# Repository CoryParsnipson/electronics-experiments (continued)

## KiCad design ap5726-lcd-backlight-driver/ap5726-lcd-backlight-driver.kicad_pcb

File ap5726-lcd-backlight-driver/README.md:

# ap5726-lcd-backlight-driver

This is a design using the AP5726 integrated chip to drive backlights on small (cellphone-sized) LCD screens. The requirements for many screens are idiosyncratic, requiring support for high voltages of up to 18-30V and 40mA of *constant* current to drive two parallel strings of 4-6 white LEDs in series.

## KiCAD Version

Current version: KiCAD 7.0.2.

This was originally made with KiCAD 7.0.2.

## Description

The backlight in LCD displays ranging from 3-7 inches in size consist of two rows of white surface mount LCDs in parallel, spanning the top and bottom edges of the screen. Each branch contains 3-6 LEDs. The LCD screen also has special diffuse material that lets the light from the LEDs spread out across the surface of the screen. One may think of the backlight in a schematic as such:

The specifications here claim that the LEDs should be driven with a maximum of 40mA of current, and the voltage drop across the entire LED circuit will be 18.2V. You can drive with lower current, and the screen will be less bright.

It is important to find a dc-converter or regulated power supply that is specifically constant current so that the screen backlight will not flicker randomly during operation.

### Schematic

The schematic of this breakout board is fairly minimal and based on [page 12 of the AP5726 datasheet](https://www.diodes.com/assets/Datasheets/AP5726.pdf).

My schematic has the addition of a solder jumper on the LED\_K pin and a test pad on the FB pin. This is because the intention is to dim the lights using the ENABLE pin, but in case I wanted to use a filtered pwm signal, I would be able to splice a voltage and resistor with the solder jumper.

For more information about this, see the "LED Dimming" section below.

#### Inductor Selection

The datasheet recommends inductors between 10 and 22 uH (micro henries). The inductor should have low core losses at 1.2 MHz and low DCR (copper wire resistance). Lastly the inductor's current saturation should exceed the peak input current of the design.

The recommended parts from the AP5726 datasheet were mostly obsolete or out of stock. I ended up using the [LQH44PN220](https://www.digikey.com/en/products/detail/murata-electronics/LQH44PN220MPRL/16516913), which seems to satisfy all of the constraints described above. (290milliOhm DCR and saturation current at 1.05A)

##### Calculating Peak Input Current and Minimum Input Current

The calculation of peak and minimum input current is partially described [here](https://components101.com/articles/boost-converter-basics-working-design#:~:text=a%20boost%20converter.-,Boost%20Converter%20Design,and%20current%20independently%2C%20the%20product%20of%20which%20is%20our%20output%20power.,-STEP%20%E2%80%93%202).

> STEP – 1
> 
> To begin with, we need a thorough understanding of what our load requires. It is highly recommended (from experience) that if you attempt to build a boost converter at the beginning it is very important to know the output voltage and current independently, the product of which is our output power.
> 
> STEP – 2
> 
> Once we have the output power, we can divide that by the input voltage (which should also be decided) to get the average input current needed.
> 
> We increase the input current by 40% to account for ripple. This new value is the peak input current.
> 
> Also the minimum input current is 0.8 times the average input current, so multiply the average input current by 0.8.
> 
> Now that we have peak and minimum current, we can calculate the total change in current by subtracting the peak and minimum current.

We can work backwards for our application. We know that we need to deliver 40mA of current to the LEDs, which will have approximately 18.2V across them.

`P = i * v = 0.04 * 18.2 = 0.728 Watts`

Now for step 2, dividing the output power by input voltage, which will be 3.3V here. (5V will work too, but my design is going to be powered by a 3.3V supply).

`I_avg = 0.728 / 3.3 = 0.221 Amps`

So next nominal peak input current is this average value times 140%:

`I_peak_nom = 0.221 * 1.4 = 0.309 Amps`

But we must also take into account the efficient of our converter (it's about 75-80% according to the datasheet). So lets go with 70% to be safe, meaning we need to multiply by 1.43:

`I_peak = 0.309 * 1.43 = 0.441 Amps`

And to get minimum input current, we can multiply average input current by 0.8 and 1.43 to account for converter efficiency:

`I_min = 0.221 * 0.8 * 1.43 = 0.252 Amps`

Now that we know peak and minimum input current, we can see that the saturation current of the inductor, which is 1.05A, is well above anything we can expect.

Also, the 18.2V @ 40mA screen is one of a few I'm intending to drive, with the most power intensive being a screen that has a voltage drop of 30V @ 40mA. This screen has a peak current of 0.8A-ish. So it's good that this inductor seems to be able to handle quite a few different situations.

#### Capacitor Selection

Small X5R or X7R ceramic surface mount capacitors are recommended for this. An output and input capacitor of 1uF should be sufficient, according to the datasheet, however, for high current applications, one may want to use 2.2uF - 4.7uF for the output capacitor to minimize output ripple.

Generic [1uF ceramic SMD capacitors in 0805 (2012 metric) from digikey](https://www.digikey.com/en/products/detail/samsung-electro-mechanics/CL21B105KAFNNNE/3886724) were sufficient.

[What does X5R, X7R, Y5V, Z5U mean for capacitors?](https://www.allaboutcircuits.com/technical-articles/x7r-x5r-c0g...-a-concise-guide-to-ceramic-capacitor-types/)

#### Diode Selection

Schottky diodes were recommended for their low forward voltage drop and fast reverse recovery. Look for a diode with low capacitance to reduce switching losses at 1.2MHz. A diode rated for 200-300 mA is supposed to be sufficient.

[BAT-43 form factor SMD schottky diodes](https://www.digikey.com/en/products/detail/micro-commercial-co/BAT43W-TP/717224) were used in my assembly.

#### R\_set Selection

The output current of the AP5726 is configurable by setting the value of Rset, on the FB pin. There is a chart showing how to calculate this value on page 9 of the [AP5726 datasheet](https://www.diodes.com/assets/Datasheets/AP5726.pdf). For us, we want 7.5 Ohms for 40 mA output. The datasheet also recommends 1% precision resistors.

A [1% 7.87 Ohm 0805 SMD resistor](https://www.digikey.com/en/products/detail/vishay-dale/CRCW08057R87FKEA/1961753) was chosen for this. Remember, getting slightly above the 7.5 value will translate to slightly less current (and slightly less maximum brightness). It is preferred to err on this side, rather than having slightly too much current.

> NOTE: At the time of initial prototyping, a 7.87 Ohm resistor was probably the closest E96 series resistor to 7.5 Ohms that was available. A quick look on Digi-Key, for instance, shows that 7.5 Ohm resistors with 1% tolerance and exactly the same form factor and dimensions are abundantly available. 

### PCB layout

There are some EMI and high frequency considerations for this particular design. The [LT1932 datasheet](https://www.analog.com/media/en/technical-documentation/data-sheets/1932f.pdf) has some really good tips on page 9. The LT1932 is a very similar chip to the AP5726.

In KiCAD, I used copper fill zones to encapsulate VCC and GND, as depicted in the LT1932 datasheet. The entire back of the PCB is a ground copper pour.

The AP5726 is physically *very* small.

The components are small and it is recommended to assemble the board using flux and a soldering iron with an SMD tip. You will also need a hotplate or hot air rework station to solder the LQH44PN220 inductor, since the pads are completely underneath the component.

### Testing

Using an Arduino Pro Micro as a USB power supply (at 4.5V), the backlight driver powers 2 parallel branches of 6 LEDs in series. The basic PCB functionality is successful!

### LED Dimming

There are several methods described by the AP5726 datasheet that can be used to partially dim the LEDs:

1. Tie EN directly to VCC or GND to enable/disable respectively. There is no gradual dimming with this method.
1. Using a PWM signal to EN. The EN pin expects a PWM signal with frequency <= 2 kHz. The average LED current increases proportionally to the duty cycle of the PWM. 0% duty cycle corresponds to "off" and 100% duty cycle is maximum brightness.
1. Using a DC Voltage (or a filtered PWM signal). This is done by supplying a DC voltage to the FB pin via a 100k resistor, and hooking up a 5k resistor to the LED anode. There is a diagram on page 11 of the AP5726 datasheet portraying this. A PWM signal filtered with a low pass filter can be used to supply the DC voltage.
1. Logic signal. If one needs only a few discrete brightness level, then using discrete transistors and digital signals into their gates may work.

Using a PWM signal seems like the easiest, most flexible way to provide dimming. One may use the PWM output capabilities of an Arduino or Raspberry Pi. Unfortunately for this design, it is intended to be connected to a Raspberry Pi that is already using the analog outputs for speaker audio. Thus, the PWM signal generation must be handled by separate hardware.

The [555-timer-pwm-generator](/555-timer-pwm-with-digipot) project was created to serve this purpose, but unfortunately the inherent design using a 555 timer does not have a wide enough duty cycle range to function well enough. Using a direct voltage divider design with the digipot barely worked, but was also too expensive, used too many components and was dependent on a specific voltage level that would have to be adjusted on a per-project basis.

The [attiny402-i2c-pwm-generator](/attiny-402-i2c-pwm-generator) project is a far superior approach using a very small microcontroller to achieve a clean, adjustable PWM signal. See this project for how the component was designed and how it is connected to the AP5726.

Later LCD related projects will combine this project and the pwm generator functional blocks in a similar way.

## References/Further Reading

* [ap5726 Datasheet](https://www.diodes.com/assets/Datasheets/AP5726.pdf)
* [lt1932 Datasheet](https://www.analog.com/media/en/technical-documentation/data-sheets/1932f.pdf)
* [Calculation of Peak and Minimum Input Current](https://components101.com/articles/boost-converter-basics-working-design#:~:text=a%20boost%20converter.-,Boost%20Converter%20Design,and%20current%20independently%2C%20the%20product%20of%20which%20is%20our%20output%20power.,-STEP%20%E2%80%93%202)
* [What does X5R, X7R, Y5V, Z5U mean for capacitors?](https://www.allaboutcircuits.com/technical-articles/x7r-x5r-c0g...-a-concise-guide-to-ceramic-capacitor-types/)

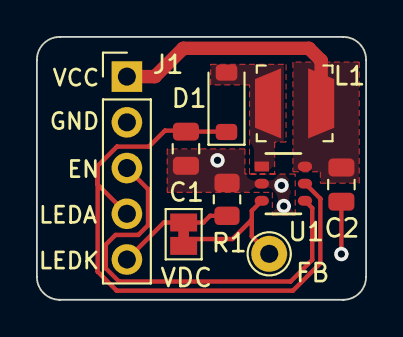
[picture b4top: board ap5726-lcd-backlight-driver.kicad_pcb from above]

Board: 2 copper layers, 18.3 x 14.6 mm, 9 parts (0 on the bottom side), 7 nets.

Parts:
C1, C2: 1uF; C_0805_2012Metric
D1: D_Schottky; D_SOD-123
FB: TestPoint; TestPoint_THTPad_D2.0mm_Drill1.0mm
J1: Conn_01x05_Pin; PinHeader_1x05_P2.54mm_Vertical
L1: 22uH; lqh44pn220mprl
R1: 7.78; R_0805_2012Metric
U1: ap5726-sot26
VDC: Jumper_2_Bridged; SolderJumper-2_P1.3mm_Bridged_Pad1.0x1.5mm

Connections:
/ENABLE: J1.3, U1.4 (EN)
/LED_A: C1.1, D1.1 (K), J1.4, U1.5 (OVP)
/LED_K: J1.5, R1.2, VDC.1 (A)
GND: C1.2, C2.2, J1.2, R1.1, U1.2 (GND)
unnamed: D1.2 (A), L1.1, U1.1 (SW)
unnamed: FB.1, U1.3 (FB), VDC.2 (B)
VCC: C2.1, J1.1, L1.2, U1.6 (Vin)

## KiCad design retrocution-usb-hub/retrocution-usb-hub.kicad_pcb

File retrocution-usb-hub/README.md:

# retrocution-usb-hub

The usb hub design uses an FE1.1s integrated USB 2.0 controller with the board layout heavily referenced from [Retrocution](https://www.retrocution.com/2020/01/15/easy-diy-tiny-usb-hub-for-raspberry-pi-projects/). Many thanks to Retrocution!

## KiCAD Version

Current version: KiCAD 7.0.2.

This was originally made with KiCAD 5.

## Description

This project was to learn how to create a PCB using KiCAD. The USB hub project was chosen because it was a good balance of simple and complex and produced a useful item at the end. This pcb actually contains three designs that were separated by mouse bites and edge cuts.

### USB Hub Design

This design uses the FE1.1s integrated chip and the design is heavily inspired by retrocution.

#### CAUTION: USB ports symbols have pins that are mirrored inadvertently!

It was found out in the assembly phase that the symbols for the USB sockets have pins that are in the wrong orientation. This means that the USB sockets must be wired to the *back* of the pcb (on the opposite side of the surface mount components) for it to work properly. Not doing this will result in the USB ports shorting VCC to ground and that will damage the host computer if power surge protection is not present on the host machine ports.

This was... quite a learning experience.

#### CAUTION: This usb hub requires a male USB A to USB A cable.

For those who don't know, a male USB A to A cable is really dangerous. Because many USB devices are designed to be hosts, plugging two hosts together with this type of cable may do damaged to one or both devices. Most cables have a female and male side, for good reason. There is rarely a good reason to have this type of cable around.

This was another learning experience... The board was designed and the upstream USB port was made to be a female socket when it should have been a male socket.

### DPad Tactile Switch Design

This is the second design (lower left on the schematic pictured above). This is a pcb footprint for game controllers that spread out four tactile switches in a cross pattern for the directional pad. The two sides of the switches are broken out into pin header at the side so they can be wired to GPIO of a microcontroller. The dimensions of this dpad layout is taken from the New Nintendo 3Ds and is similar (but slightly smaller than) that of the Nintendo Switch.

The tactile switches in this design were [Omron B3F-1000](https://www.digikey.com/en/products/detail/omron-electronics-inc-emc-div/B3F-1000/33150).

This design also requires a custom designed 3d printed part that sits in the middle. You can find a Fusion 360 model of this part in `retrocution-usb-hub/lib/models/tactile-switch-abxy/abxy-pcb-jig v1.3fd`. The purpose of the 3d printed part is so that the soft silicoe membrane can rest flush to the top of the switches. It is meant for new nintendo 3ds ABXY buttons to go on top of the membrane. A properly shaped enclosure should hold everything in place.

Example pictures. Models are not included in this repo.

### DPad Copper Footprint Design

The third design, imo, is most interesting. This is a footprint for traces that can interface with "metal dome switches" for compact controller buttons. (See References for more information).

This requires many parts in addition to just the PCB:

* New 3DS Metal Dome Switch Membrane (https://www.aliexpress.us/item/2251832833816917.html)
* New 3DS Replacement DPad (https://www.aliexpress.us/item/3256802328844124.html)
* New 3DS Silicone Membrane (https://www.aliexpress.us/item/2251832866142244.html)
* Right Angle male pin header

Despite all the window dressing, the point of this project is to see whether or not one could reproduce the copper pcb trace to interface with the metal dome switches. The footprint consists of a ring with a rectangular protrusion on the side that is a custom imported SVG image made in a graphics program like Inkscape. The second half of the pin is a smaller round pad in the center. In the outer footprint, this center pad is connected to the back copper using a via and all the back traces are connected together in a diamond shape and then routed to the pin header as pin #5. And, obviously, the precise sizes of the middle circles and rings and their relative spacing is very important to get correct to fit to the 3ds dpad.

## References/Further Reading

* [A Quick Guide to Tactile Metal Dome Switches](https://www.snaptron.com/2022/12/quick-guide-to-tactile-metal-domes-switches-snaptron/)  
  Metal dome switches are used to make compact electronics with nice buttons. This is especially common in portable game consoles and game controllers. The nintendo 3ds uses metal dome switches embedded in a sticker that is adhered to a trace on a PCB.

* [Circular pad in KiCAD](https://forum.kicad.info/t/circular-pad-in-kicad/12689)  
  This is a really useful stackexchange question about how to make a custom pin footprint. This is specifically about how to make a pin that resembles the trace you need to make contact with a "metal dome switch". This advice was used to make a working dpad footprint.

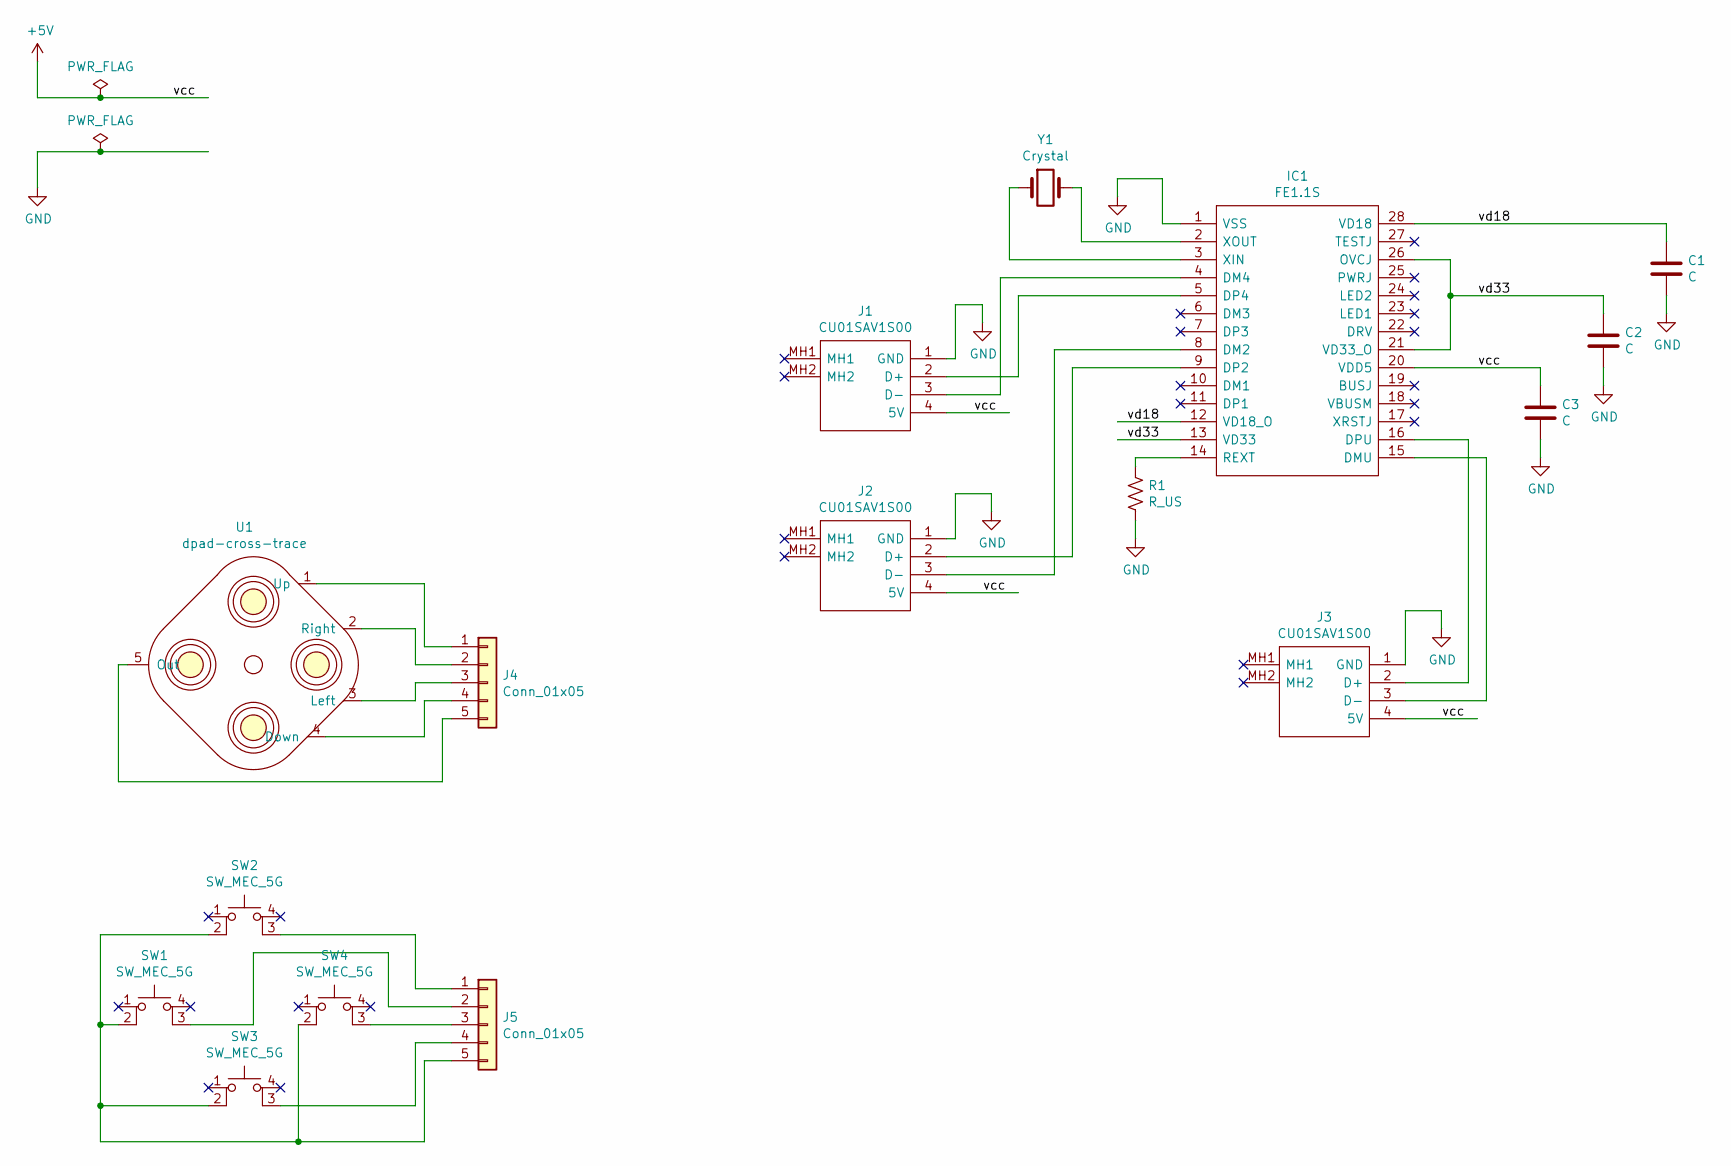
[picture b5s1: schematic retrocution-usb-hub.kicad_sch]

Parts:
C1, C2, C3: C; C_0603_1608Metric
IC1: FE1.1S; SOP64P600X175-28N; Manufacturer_Part_Number FE1.1S
J1, J2, J3: CU01SAV1S00; Manufacturer_Part_Number CU01SAV1S00
J4, J5: Conn_01x05; PinHeader_1x05_P2.54mm_Vertical
R1: R_US; R_0603_1608Metric
SW1, SW2, SW3, SW4: SW_MEC_5G; SW_TH_Tactile_Omron_B3F-10xx
U1: dpad-cross-trace; 3ds_dpad_cross
Y1: Crystal; Crystal_HC49-4H_Vertical

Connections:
+5V: C3.1, IC1.20 (VDD5), J1.4 (5V), J2.4 (5V), J3.4 (5V)
/vd18: C1.1, IC1.12 (VD18_O), IC1.28 (VD18)
/vd33: C2.1, IC1.13 (VD33), IC1.21 (VD33_O), IC1.26 (OVCJ)
GND: C1.2, C2.2, C3.2, IC1.1 (VSS), J1.1 (GND), J2.1 (GND), J3.1 (GND), R1.2
unnamed: IC1.2 (XOUT), Y1.2
unnamed: IC1.3 (XIN), Y1.1
unnamed: IC1.4 (DM4), J1.3 (D-)
unnamed: IC1.5 (DP4), J1.2 (D+)
unnamed: IC1.8 (DM2), J2.3 (D-)
unnamed: IC1.9 (DP2), J2.2 (D+)
unnamed: IC1.14 (REXT), R1.1
unnamed: IC1.15 (DMU), J3.3 (D-)
unnamed: IC1.16 (DPU), J3.2 (D+)
unnamed: J4.1, U1.1 (Up)
unnamed: J4.2, U1.2 (Right)
unnamed: J4.3, U1.3 (Left)
unnamed: J4.4, U1.4 (Down)
unnamed: J4.5, U1.5 (Out)
unnamed: J5.1, SW2.3 (K)
unnamed: J5.2, SW1.3 (K)
unnamed: J5.3, SW4.3 (K)
unnamed: J5.4, SW3.3 (K)
unnamed: J5.5, SW1.2, SW2.2, SW3.2, SW4.2

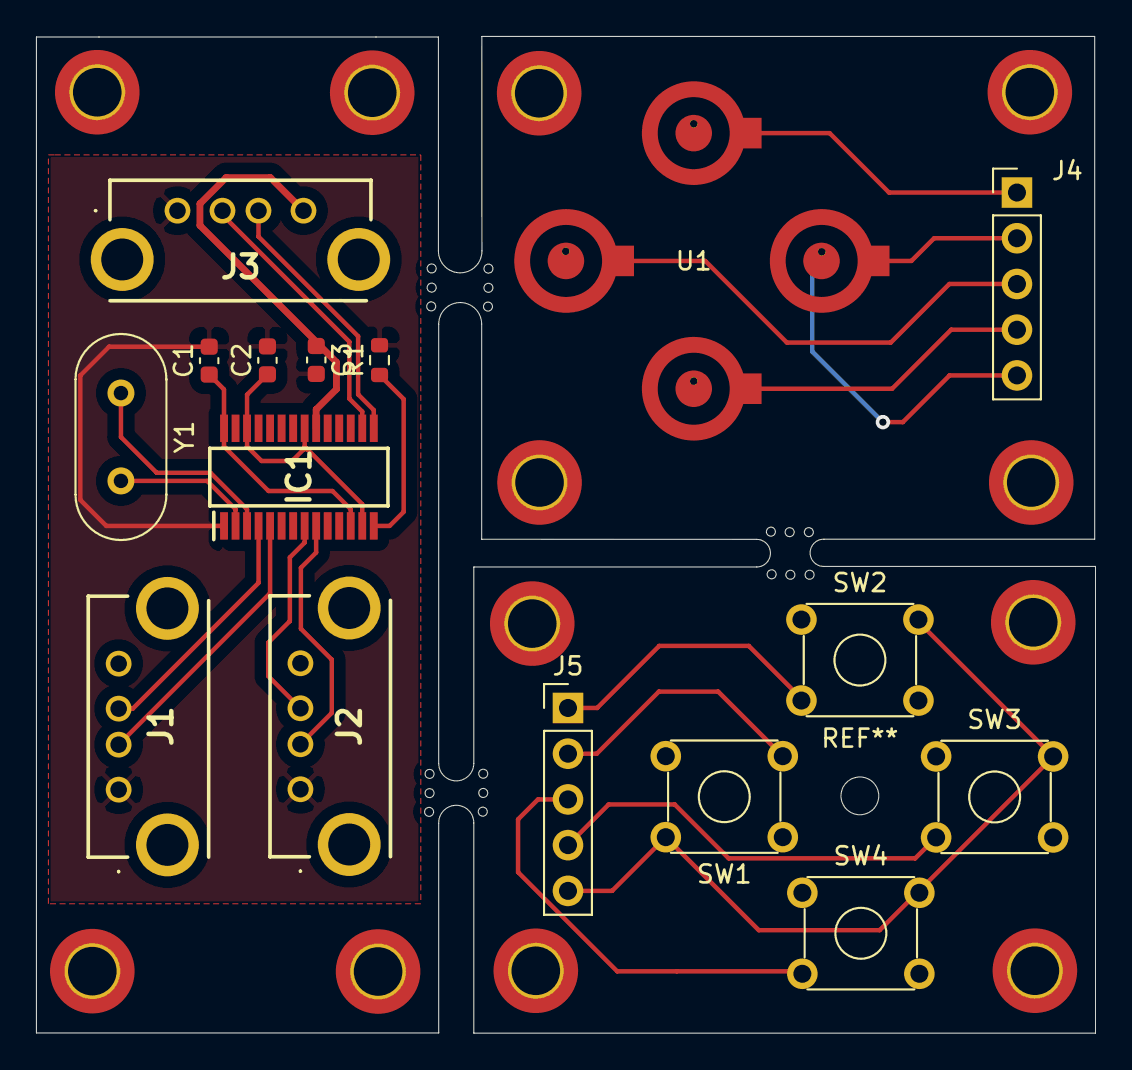
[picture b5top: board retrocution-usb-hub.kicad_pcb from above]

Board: 2 copper layers, 58.8 x 55.4 mm, 16 parts (0 on the bottom side), 23 nets.

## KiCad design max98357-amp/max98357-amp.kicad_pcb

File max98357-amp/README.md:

# max98357-amp

This is a PCB for a speaker amplifier heavily based on a [product by Adafruit](https://learn.adafruit.com/adafruit-max98357-i2s-class-d-mono-amp). The PCB design is essentially exactly the same but with extra resistors wiring to bias certain input pins for convenience of testing different configurations.

## KiCAD Version

Current version: KiCAD 7.0.2.

This was originally made with KiCAD 6.0.7.

## Description

The IC used here is a variant of the MAX98357 Audio Power Amplifier [MAX98357AETE+T](https://www.newark.com/maxim-integrated-products/max98357aete-t/audio-power-amp-d-40-to-85deg/dp/82AC2949), a 16 pin TQFN package that must be soldered using surface mount techniques. (I used a hot air gun and solder paste).

### SD\_MODE

The first large modification is three jumpers with resistors to bias input voltage going into the SD\_MODE input. SD\_MODE controls whether or not the amplifier outputs a stereo average, left channel, or right channel of the input sound data. The resistor values are calculated based on 3.3V input rail. Refer to the [datasheet](https://cdn-shop.adafruit.com/product-files/3006/MAX98357A-MAX98357B.pdf) for more information.

### Differential Output Test Pins

This PCB also includes two pin holes going to the + and - outputs of the amplifier. Mainly for "test pins" so you can probe into the signal for whatever reason. Originally this was so that a 3.5mm headphone jack socket could be connected to it later.

For more detailed explanation, refer to [the blog posts here](https://forums.somethingawful.com/showthread.php?threadid=3947328&pagenumber=11#post527927218).

### Getting Volume Control to work on Raspberry Pi OS (Raspbian)

You may notice that the volume control does not actually change the volume coming out of the speaker, even after ALSA has been set up. Mute may or may not work. That is because Linux has been gradually switching over to use Pulse Audio and something broke over the years. Even the Adafruit documentation does not have a solution for this.

Luckily, I spent like two weeks trying to figure out what went wrong and I have a fix for it.

Create a file on the system called `/etc/asound.conf`:

```
pcm.speakerbonnet {
   type hw card 0
}

pcm.dmixer {
   type dmix
   ipc_key 1024
   ipc_perm 0666
   slave {
     pcm "speakerbonnet"
     period_time 0
     period_size 1024
     buffer_size 8192
     rate 48000
     channels 2
   }
}

ctl.dmixer {
    type hw card 0
}

pcm.softvol {
    type softvol
    slave.pcm "dmixer"
    control.name "PCM"
    control.card 0
}

ctl.softvol {
    type hw card 0
}

pcm.!default {
    type             plug
    slave.pcm       "softvol"
}
```

This will give you a software controlled volume on your operating system output.

Next change `/usr/share/pulseaduio/alsa-mixer/paths/analog-output.conf.common` from:

```
[Element PCM]
switch = mute
volume = merge
override-map.1 = all
override-map.2 = all-left,all-right  
```

to

```
[Element PCM]
switch = mute
volume = ignore
```

What I think this does is tell pulse to ignore the volume controls on the alsa softvol device. Then because that happened, pulse's internal software mixer kicks in.

## References/Further Reading

* [max98357 Datasheet by Analog](https://www.analog.com/media/en/technical-documentation/data-sheets/MAX98357A-MAX98357B.pdf)  
  IC datasheet

* [Adafruit Documentation for MAX98357 I2S Class-D Mono Amp](https://learn.adafruit.com/adafruit-max98357-i2s-class-d-mono-amp/overview)  
  Extremely useful documentation for usage of this amplifier. The design in this repo is basically copied from this.

* [What is a Class-D Amplifier and What Are they Useful For?](https://www.howtogeek.com/792135/what-is-a-class-d-amplifier-and-what-are-they-useful-for/)  
  This is an informative page for briefly explaining Class-D Amps.

* [Volume Control for MAX98357 class D amp not working](https://forums.raspberrypi.com/viewtopic.php?t=341471)  
  A link to my thread on the Raspberry Pi forums where I debug why volume control wasn't working for this amplifier when using Raspberry Pi OS (Raspbian).

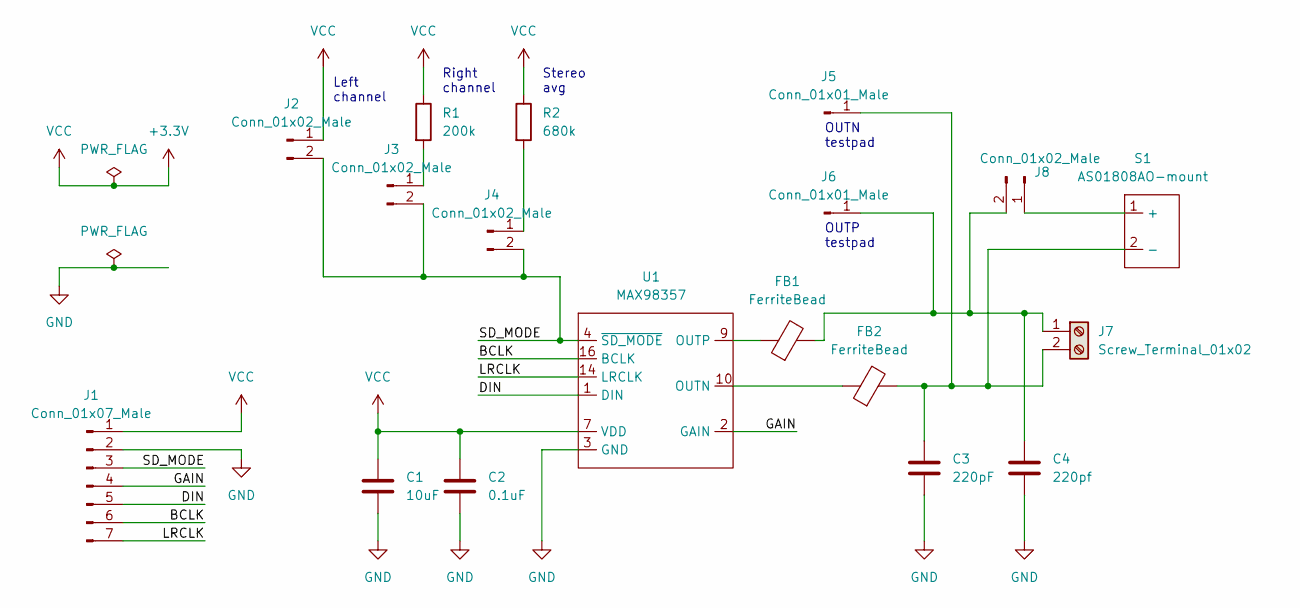
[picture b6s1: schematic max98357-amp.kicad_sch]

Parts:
C1: 10uF; C_0603_1608Metric
C2: 0.1uF; C_0603_1608Metric
C3: 220pF; C_0603_1608Metric
C4: 220pf; C_0603_1608Metric
FB1, FB2: FerriteBead; R_0603_1608Metric
J1: Conn_01x07_Male; PinHeader_1x07_P2.54mm_Vertical
J2, J3, J4, J8: Conn_01x02_Male; PinHeader_1x02_P2.54mm_Vertical
J5, J6: Conn_01x01_Male; PinHeader_1x01_P2.54mm_Vertical
J7: Screw_Terminal_01x02; TerminalBlock_Phoenix_PT-1,5-2-3.5-H_1x02_P3.50mm_Horizontal
R1: 200k; R_0603_1608Metric
R2: 680k; R_0603_1608Metric
S1: AS01808AO-mount
U1: MAX98357; MAX98357-TQFN16-T1633+4

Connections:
+3.3V: C1.1, C2.1, J1.1, J2.1, R1.1, R2.1, U1.7 (VDD), U1.8
/BCLK: J1.6, U1.16 (BCLK)
/DIN: J1.5, U1.1 (DIN)
/GAIN: J1.4, U1.2 (GAIN)
/LRCLK: J1.7, U1.14 (LRCLK)
/SD_MODE: J1.3, J2.2, J3.2, J4.2, U1.4 (~SD_MODE)
GND: C1.2, C2.2, C3.2, C4.2, J1.2, U1.3 (GND), U1.11, U1.15, U1.17
unnamed: C3.1, FB2.2, J5.1, J7.2, S1.2 (-)
unnamed: C4.1, FB1.2, J6.1, J7.1, J8.2
unnamed: FB1.1, U1.9 (OUTP)
unnamed: FB2.1, U1.10 (OUTN)
unnamed: J3.1, R1.2
unnamed: J4.1, R2.2
unnamed: J8.1, S1.1 (+)

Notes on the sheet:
Right channel
Left channel
OUTP testpad
OUTN testpad
Stereo avg

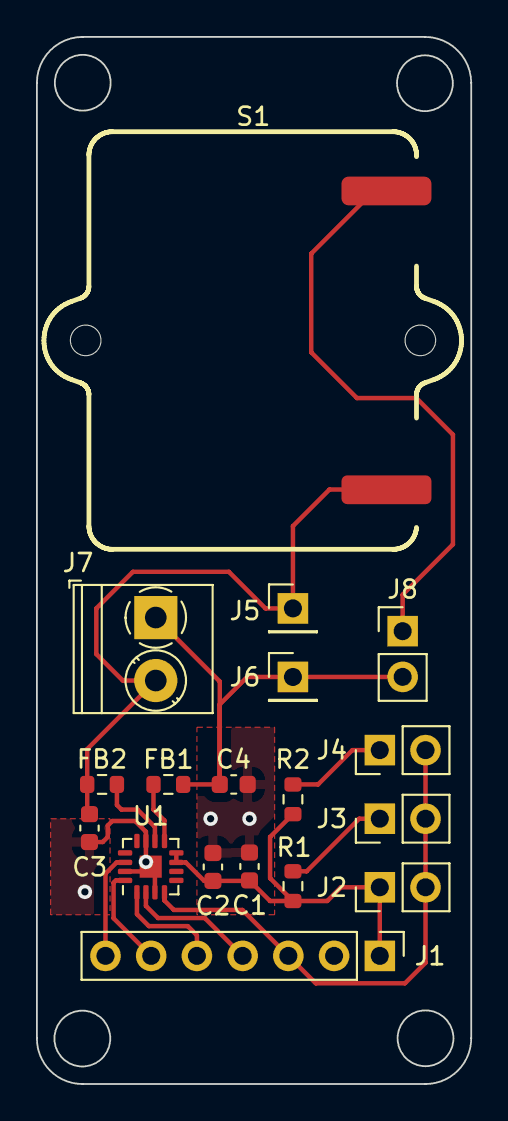
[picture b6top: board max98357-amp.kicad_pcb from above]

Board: 2 copper layers, 24.1 x 58.2 mm, 18 parts (0 on the bottom side), 14 nets.

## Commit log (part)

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2023-02-11 Add two audio experiments.
2023-02-11 Fix image links.
2023-02-11 Add note about KiCAD 6.
2023-02-11 Add model for back of as01808ao-enclosure.
2023-04-22 Upgrade as01808ao-enclosure to KiCAD 7.
2023-04-22 Update MAX98357 project to KiCAD 7.
2023-04-24 Change image paths and small formatting changes.
2023-04-24 Add retrocution-usb-hub project.
    The name isn't the most accurate, since the pcb is actually 3 pcb
    projects in one. This also contains ABXY and dpad tests, which I think
    are much more interesting.
2023-06-27 Add KiCAD project and README for ap5726 project.
2023-07-02 Add schematic and symbols for ap5726 project.
2023-07-02 Add testpoint and jumper to feedback on AP5726.
2023-07-03 Add all footprints except inductor.
    Import footprint and step model for AP5726 from mouser.
2023-07-03 Initial PCB layout and footprint fixes for AP5726.
    Note to self: maybe we should ask EEVblog forum members for a PCB layout
    critique? Could be painful...
2023-07-03 Add footprints for 555 timer.
    555 timer needed custom footprint. Downloaded model off the internet
    somewhere.
    The digipot seems to fit the MSOP-10_3x3mm_P0.5mm footprint and model
    from preloaded library.
2023-07-04 Fix and add more material to 555-timer readme.
2023-07-05 Small changes to 555-timer pcb layout.
2023-07-05 More AP5726 pcb layout changes.
2023-07-05 Move via off pad of C2 in AP5726 design.
    Apparently, it's not good to put vias directly on pads (metal dome
    switch trace design being an exception) because it may wick away solder
    and also cause the surface to be uneven. An exception to this is when
    you have a large thermal pad underneath an IC, in which case you may
    want many vias spread out to provide surface area for solder to contact
    as well as provide better heat distribution to the copper area on the
2023-07-05 More small fill zone mods in ap5726.
2023-07-05 Small pcb layout changes to 555-timer pwm design.
2023-07-18 Update README of the AP5726 project.
2023-07-18 Small change to ap5726 readme.
2023-07-18 Add two new projects to main README.
2023-08-12 Fill out most of 555-timer-pwm-with-digipot README.
    Include post mortem. This experiment is a failure. :(
2023-08-12 555-timer readme changes.
    Add links to the explanations instead of using just [1] and [2] to be
    more consistent with the rest of the repository.
2023-08-12 Try fixing video urls in 555-timer readme.
2023-08-12 Small changes to 555-timer readme.
    1. Add reference to how microcontrollers generate pwm signals for
    complete-ness
    2. Fix broken image.
2023-08-12 Use subscripts for resistor names in 555-timer readme.
2024-03-23 Fix typo.
2024-03-23 Implement EEPROM and I2C -> PWM control in attiny402 firmware.
2024-03-24 Add more serial debug messages. Minor refactors.
2024-03-24 Add helpful eeprom debugging sketches.
2024-03-24 Implement config register variable handling.
    You can use INVERT MODE and switch between 8 and 16 bit duty cycle.
    See code comments for usage information.
2024-03-25 Correct invert mode handling.
    The test circuit logic was inverted and not the on board peripheral.
2024-03-26 Add out of bounds check to i2c pwm firmware.
2024-04-08 Add bash script to test led brightness via I2C.
2024-04-15 Implement periodic eeprom writeback.
    Simulate "watchdog" timer so that you only write back to eeprom after a
    short time of no register changes (10 sec here). This will prolong the
    lifetime of the eeprom cells by a lot, and also make it more responsive,
    since it's not writing to eeprom all the time.
    Include a second watchdog timer that writes back to eeprom even if there
    is sustained register write activity. This timeout is 1 min. (So if
2024-04-15 Change main loop delay to 1ms.
    The `delay()` function is apparently blocking?
2024-06-25 Add links to main readme.
2024-06-25 Update intro to PWM generator readme.
2024-06-25 Fix image link.
2024-06-25 Add UPDI and programming info for PWM generator project.
2024-06-25 Fix broken image link.
2024-06-27 Fill in hardware setup information for I2C PWM generator.
2024-06-27 More README changes.
2024-06-27 Add most firmware notes in PWM I2C generator README.
2024-06-27 I2C PWM Generator README edits.
2024-06-27 Add linebreaks to image captions.
2025-07-11 Fix some errors in the ap5726 backlight project README.
2025-07-13 Elaborate on some ambiguous points in README
    Elaborate on some abiguous points in the README of the attiny 402 i2c
    pwm generator repo.
2025-07-25 Add more comments to mipi-dsi-breakout readme.
2025-07-25 Add two lcd screen connector symbols.
2025-07-25 Add names to lcd connectors and fix errors.
2025-07-26 Remove 4.7kOhm resistor from UDPI pin.
    This should be part of the programmer PCB instead of the
    host-side-interface.
2025-07-26 Change PWM symbol to attiny402.
    Be more specific about which part it should be.
    Also fix ERC issue with AP5726 on the host-side-interface with
    unconnected schottky diode.
2025-07-27 Layout schematic for lcd side interface.
    Also change most pins on the mipi 20 pin header interface connector to
    bidirectional to avoid ERC headache.
2025-08-06 Hook up step models to footprints.
    Also add new footprint for sus grounding pad.
2025-08-08 Fill out lcd side interface + double check errors.
    * Flip orientation of most connectors to match orientation of real world
    parts.
    * Added NC pins to symbol so they are matched up to the footprints.
    * Added a RESET_FAILSAFE solder bridge that can be cut in the case that
    the CTP touch screen resets aren't active low and the DSI resets are.
    * Double check pin ordering and reset signals.
2025-08-13 Fix footprint model z offset.
2025-08-13 Flip orientation of 40pin zif pads.
    The connector footprint is on the wrong side (cable goes in the opposite
    side of the lever). Flip the pads to original orientation to match
    part...
    Add user drawings annotation and measurements to lcd side pcb.
2025-08-14 Resolve non-connection related DRC issues.
    Change minimum pad clearance to be 0.175mm because 0.2mm is too large.
    (In this case the footprints need smaller clearance because the pitch is
    set.)
    Ignore bridged aperature front solder mask on zif connectors for
    basically the same reason.
2025-08-15 Remove solder mask expansion on all zif pads.
    This 0.102 value comes from the part footprint, I think and it quite
    conservative. Checking with pcbway and jlcpb, they both can do solder
    mask bridge of < 0.20m, so they should be able to both add solder mask
    between all of these pads.
2025-08-30 Update rpi dsi connector symbol.
2025-09-06 Redo mipi dsi schematic based on new info.
    Initial plan with "lcd-side-interface" and "host-side-interface" is too
    complicated and needs rework based on information learned about how
    differential signals work.
    Create new design that will be 1 pcb for diff pair signal routing, that
    uses the 22 pin zif connector to RPi DSI directly (instead of pin
    header) and have 4 of these circuits on one PCB.
2025-09-19 First draft of dsi signal routing in mipi dsi breakout.
2025-09-19 Remove old version of mipi dsi breakout projects.
2025-09-28 Change jumper silkscreen and hole edgecuts.
2025-09-28 Change mipi-dsi-breakout README.
2025-11-21 [mipi-dsi-breakout] Add description to README.
2025-11-21 [mipi-dsi-breakout] Add more background information in README
2025-11-21 [mipi-dsi-breakout] Try different way to caption
2025-11-21 [mipi-dsi-breakout] Finish writing LCD overview.
2025-11-21 [mipi-dsi-breakout] Change title of interface section
2025-11-21 [mipi-dsi-breakout] Add info about diff pair signals.
2025-11-21 [mipi-dsi-breakout] Add transition sentence.
2025-11-26 [mipi-dsi-breakout] Do some README editing in Design Overview section.
2025-11-26 [mipi-dsi-breakout] Move part selection up and add screens.
2025-11-26 [mipi-dsi-breakout] README edits.
    Remove system design image in a couple places. It seems unnecessary.
    Fix image for 5 inch display with ctp.
2025-11-26 [mipi-dsi-breakout] Add part selection to README.
2025-11-26 [mipi-dsi-breakout] Add Assembly section to README.
2025-11-26 [mipi-dsi-breakout] Fix broken image links.
2025-11-26 [mipi-dsi-breakout] Add PCB Layout section to README
2025-12-11 [mipi-dsi-breakout] Add 5 inch dsi picture
2026-01-10 [mipi-dsi-breakout] Update readme with assembly info.
    Add pictures and files for 3d printed parts and instructions to assemble
    everything together.
    Add pictures and descriptions for the full test setup.
2026-01-10 [mipi-dsi-breakout] Fix typo in readme.
2026-01-10 [mipi-dsi-breakout] Add I2C hookup info
    Forgot to add this one last part in the readme.
2026-01-30 [mipi-dsi-breakout] Add drafts of driver and dts files.
2026-01-30 [mipi-dsi-breakout] Fix Makefile so it works.
    * Remove extra dts file in wrong folder.
    * Add .o file to obj-m, which was missing. Remove kernel src
    variable because it was not needed. Use `/lib/modules/` folder
    for make instead of kernel source, which was incorrect.
    * make should now work properly and modules_install too. Depmod
    will not work unless the whole kernel was configured and compiled
2026-02-01 [mipi-dsi-breakout] Add Makefile for dtbo compilation.
    Just to have some record of what to do.
2026-02-16 [mipi-dsi-breakout] TST043WVBI driver and device tree mods
    * Add fixed regulators to device tree fragments to get rid of regulator
    warnings in dmesg. These are fixed regulators so the init sequence
    still does not power cycle anything, but the init sequence timing
    might be more accurate. (This does not fix any current issues.)
    * Create copy of panel-ilitek-ili9806e.c driver and call it
    panel-tst043wvbi.c with custom init sequence and compatibility string.
2026-02-16 [mipi-dsi-breakout] Change dt overlay name to be more accurate
2026-03-10 [mipi-dsi-breakout] Add device tree dump target to Makefile
2026-03-10 [mipi-dsi-breakout] Remove two commands at end
    Page 0 cmd 0x21 inverts the colors and Page 0 cmd 0x36 sets some non
    default BGR (instead of RGB) mapping in the MADCTL register. These are
    commented out in the vendor's init sequence, but was accidentally added
    here.
    Fix some formatting on porch timing section.
    In addition to this fix, the screen defaults to portrait orientation.
2026-03-12 [mipi-dsi-breakout] Change wording
    Raspberry Pi CM3 is not a microcontroller, so change the wording to be
    more accurate.
2026-03-12 [mipi-dsi-breakout] Incorporate corrections from 6by9
2026-03-12 [mipi-dsi-breakout] Forgot a couple names
2026-03-13 [mipi-dsi-breakout] Fix some README typos
2026-04-09 [mipi-dsi-breakout] Add working touchscreen overlay
    Get the goodix gt911 working on the tst043wvbi-130c via device overlay
    settings. The driver is already bundled with the linux kernel.
    Use GPIO 27 as the interrupt pin, set to input with internal pull up
    resistor. Use GPIO 22 as lcd reset pin, set to output and active low
    with no internal pull up.
    Note, the screen may assume the i2c address of 0x14 or 0x5d depending on
2026-05-01 [mipi-dsi-breakout] Get /sys/class/backlight working.
    Create driver for attiny i2c pwm generator that uses I2C and regmap.
    Modify tst043wvbi device tree overlay to add backlight device hookup and
    backlight device with driver compatibility string.
    Upon rebooting, the device should show up under `/sys/class/backlight`
    with the `tst043wvbi` name. You can modify this by hand by writing to
    this file:
2026-05-01 [mipi-dsi-breakout] Add GAMMA 2.5 mapping to script.
    Used Gemini to spoon feed me this shit and it pulled out this weird
    brightness curve that looks really good.
2026-05-01 [mipi-dsi-breakout] Small modifications to brightness script.
2026-05-06 [mipi-dsi-breakout] Update README with software bringup
